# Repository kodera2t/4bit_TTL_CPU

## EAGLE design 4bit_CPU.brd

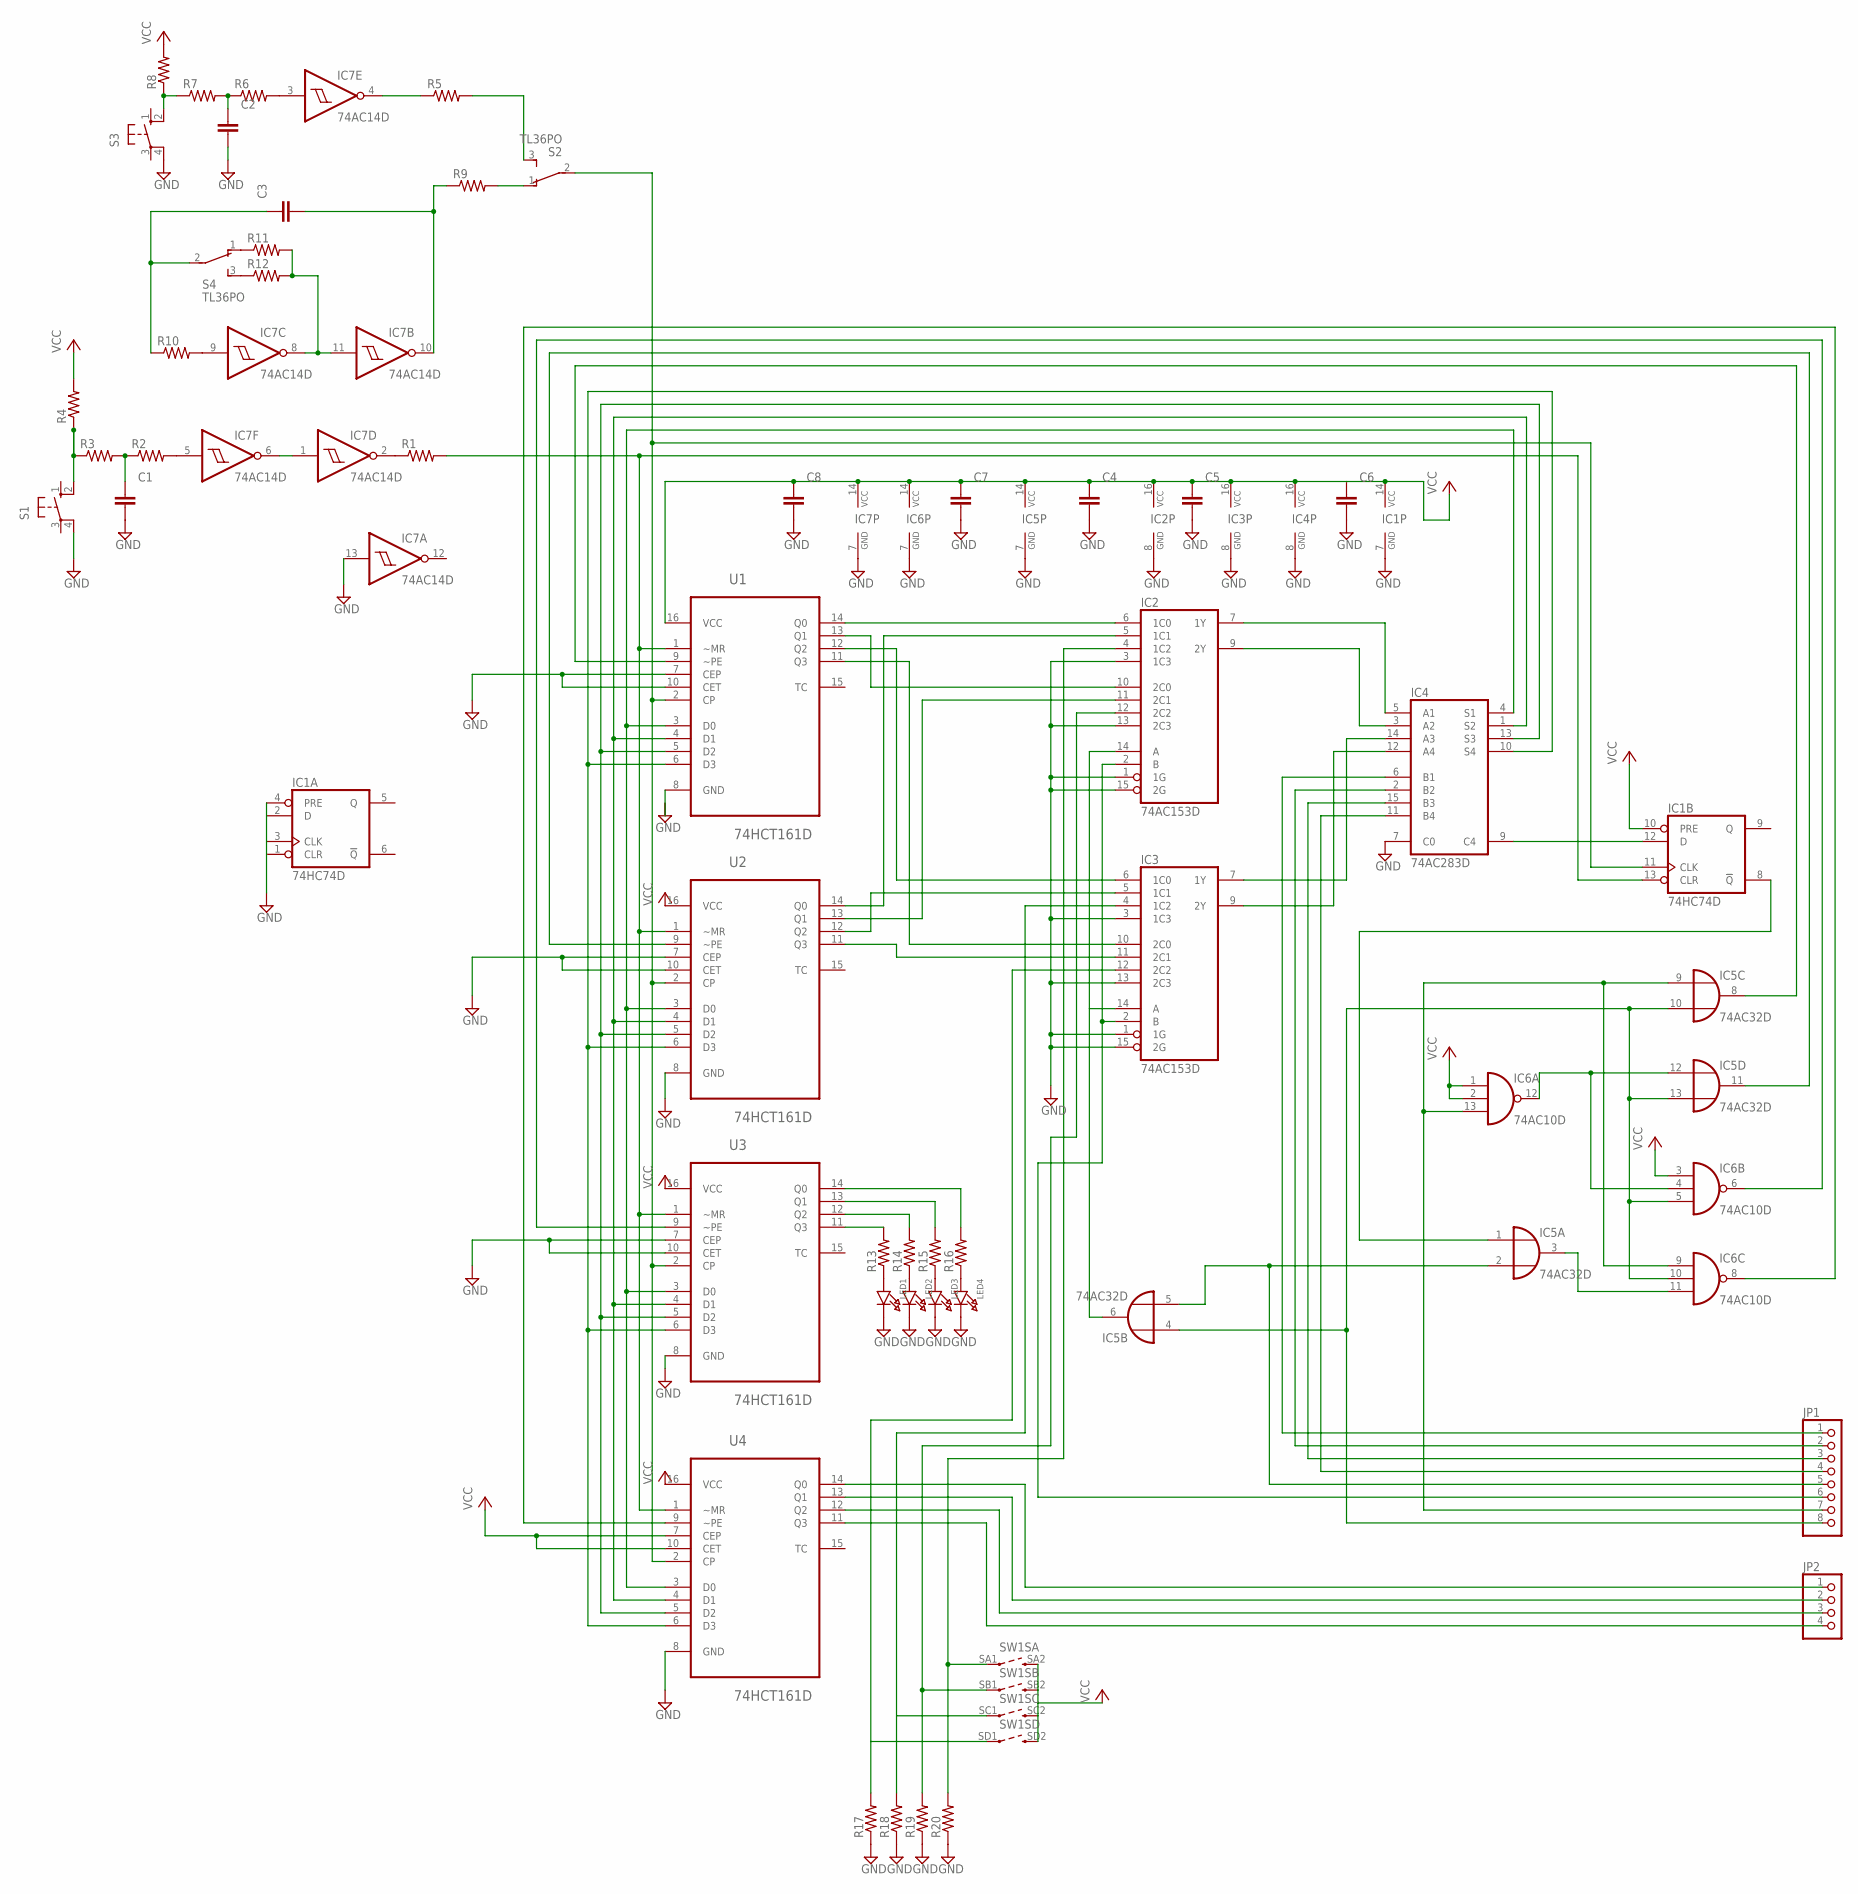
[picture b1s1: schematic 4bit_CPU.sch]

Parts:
C1, C2, C3, C4, C5, C6, C7, C8: CAPACITOR_NPOL-0603; C603
IC1: 74HC74D; SO14
IC2, IC3: 74AC153D; SO16
IC4: 74AC283D; SO16
IC5: 74AC32D; SO14
IC6: 74AC10D; SO14
IC7: 74AC14D; SO14
JP1: HEADER-1X8; 1X08_OVAL
JP2: HEADER-1X4; 1X04_OVAL
LED1, LED2, LED3, LED4: LED0603; CHIPLED_0603
R1, R2, R3, R4, R5, R6, R7, R8, R9, R10, R11, R12, R13, R14, R15, R16, R17, R18, R19, R20: R-US_R0603; R0603
S1, S3: 10-XX; B3F-10XX
S2, S4: TL36PO; TL3XPO
SW1: SW_DIP_4P; SW-SMT-4
U1, U2, U3, U4: 74HCT161D; SOIC127P600X175-16N

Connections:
GND: C1.2, C2.2, C4.2, C5.2, C6.2, C7.2, C8.2, IC1.1 (CLR), IC1.2 (D), IC1.3 (CLK), IC1.4 (PRE), IC1.7 (GND), IC2.1 (1G), IC2.3 (1C3), IC2.8 (GND), IC2.13 (2C3), IC2.15 (2G), IC3.1 (1G), IC3.3 (1C3), IC3.8 (GND), IC3.13 (2C3), IC3.15 (2G), IC4.7 (C0), IC4.8 (GND), IC5.7 (GND), IC6.7 (GND), IC7.7 (GND), IC7.13 (I), LED1.C, LED2.C, LED3.C, LED4.C, R17.1, R18.1, R19.1, R20.1, S1.4 (P1), S3.4 (P1), U1.7 (CEP), U1.10 (CET), U2.7 (CEP), U2.8 (GND), U2.10 (CET), U3.7 (CEP), U3.8 (GND), U3.10 (CET), U4.8 (GND)
unnamed: IC2.14 (A), IC3.14 (A), IC5.6 (O)
unnamed: IC2.2 (B), IC3.2 (B), JP1.6
unnamed: IC2.6 (1C0), U1.14 (Q0)
unnamed: IC2.5 (1C1), U2.14 (Q0)
unnamed: IC2.10 (2C0), U1.13 (Q1)
unnamed: IC3.6 (1C0), U1.12 (Q2)
unnamed: IC3.5 (1C1), U2.12 (Q2)
unnamed: IC3.10 (2C0), U1.11 (Q3)
unnamed: IC3.11 (2C1), U2.11 (Q3)
unnamed: IC2.11 (2C1), U2.13 (Q1)
unnamed: IC2.7 (1Y), IC4.5 (A1)
unnamed: IC2.9 (2Y), IC4.3 (A2)
unnamed: IC3.7 (1Y), IC4.14 (A3)
unnamed: IC3.9 (2Y), IC4.12 (A4)
unnamed: JP2.1, U4.14 (Q0)
unnamed: IC1.11 (CLK), S2.2, U1.2 (CP), U2.2 (CP), U3.2 (CP), U4.2 (CP)
unnamed: IC1.12 (D), IC4.9 (C4)
unnamed: IC1.13 (CLR), R1.2, U1.1 (~MR), U2.1 (~MR), U3.1 (~MR), U4.1 (~MR)
unnamed: IC4.4 (S1), U1.3 (D0), U2.3 (D0), U3.3 (D0), U4.3 (D0)
unnamed: IC4.1 (S2), U1.4 (D1), U2.4 (D1), U3.4 (D1), U4.4 (D1)
unnamed: IC4.13 (S3), U1.5 (D2), U2.5 (D2), U3.5 (D2), U4.5 (D2)
unnamed: IC4.10 (S4), U1.6 (D3), U2.6 (D3), U3.6 (D3), U4.6 (D3)
unnamed: IC5.9 (I0), IC6.9 (I0), IC6.13 (I2), JP1.7
unnamed: IC5.4 (I0), IC5.10 (I1), IC5.13 (I1), IC6.5 (I2), IC6.10 (I1), JP1.8
unnamed: IC5.12 (I0), IC6.4 (I1), IC6.12 (O)
unnamed: IC5.3 (O), IC6.11 (I2)
unnamed: IC1.8 (!Q), IC5.1 (I0)
unnamed: IC5.2 (I1), IC5.5 (I1), JP1.5
unnamed: R5.2, S2.3 (S)
unnamed: IC5.8 (O), U1.9 (~PE)
unnamed: IC5.11 (O), U2.9 (~PE)
unnamed: IC6.6 (O), U3.9 (~PE)
unnamed: IC6.8 (O), U4.9 (~PE)
unnamed: IC7.2 (O), R1.1
unnamed: IC7.1 (I), IC7.6 (O)
unnamed: IC7.5 (I), R2.2
unnamed: C1.1, R2.1, R3.2
unnamed: R3.1, R4.1, S1.2 (S1)
unnamed: IC7.4 (O), R5.1
unnamed: IC7.3 (I), R6.2
unnamed: C2.1, R6.1, R7.2
unnamed: R7.1, R8.1, S3.2 (S1)
unnamed: R9.2, S2.1 (O)
unnamed: IC7.8 (O), IC7.11 (I), R11.2, R12.2
unnamed: C3.2, IC7.10 (O), R9.1
unnamed: IC7.9 (I), R10.2
unnamed: JP2.2, U4.13 (Q1)
unnamed: R11.1, S4.1 (O)
unnamed: R12.1, S4.3 (S)
unnamed: C3.1, R10.1, S4.2
unnamed: IC4.11 (B4), JP1.4
unnamed: IC4.15 (B3), JP1.3
unnamed: IC4.2 (B2), JP1.2
unnamed: IC4.6 (B1), JP1.1
unnamed: JP2.3, U4.12 (Q2)
unnamed: JP2.4, U4.11 (Q3)
unnamed: R13.2, U3.11 (Q3)
unnamed: R14.2, U3.12 (Q2)
unnamed: R15.2, U3.13 (Q1)
unnamed: R16.2, U3.14 (Q0)
unnamed: LED1.A, R13.1
unnamed: LED2.A, R14.1
unnamed: LED3.A, R15.1
unnamed: LED4.A, R16.1
unnamed: IC2.4 (1C2), R20.2, SW1.SA1 (1)
unnamed: IC2.12 (2C2), R19.2, SW1.SB1 (1)
unnamed: IC3.4 (1C2), R18.2, SW1.SC1 (1)
unnamed: IC3.12 (2C2), R17.2, SW1.SD1 (1)
VCC: C4.1, C5.1, C6.1, C7.1, C8.1, IC1.10 (PRE), IC1.14 (VCC), IC2.16 (VCC), IC3.16 (VCC), IC4.16 (VCC), IC5.14 (VCC), IC6.1 (I0), IC6.2 (I1), IC6.3 (I0), IC6.14 (VCC), IC7.14 (VCC), R4.2, R8.2, SW1.SA2 (2), SW1.SB2 (2), SW1.SC2 (2), SW1.SD2 (2), U1.16 (VCC), U2.16 (VCC), U3.16 (VCC), U4.7 (CEP), U4.10 (CET), U4.16 (VCC)

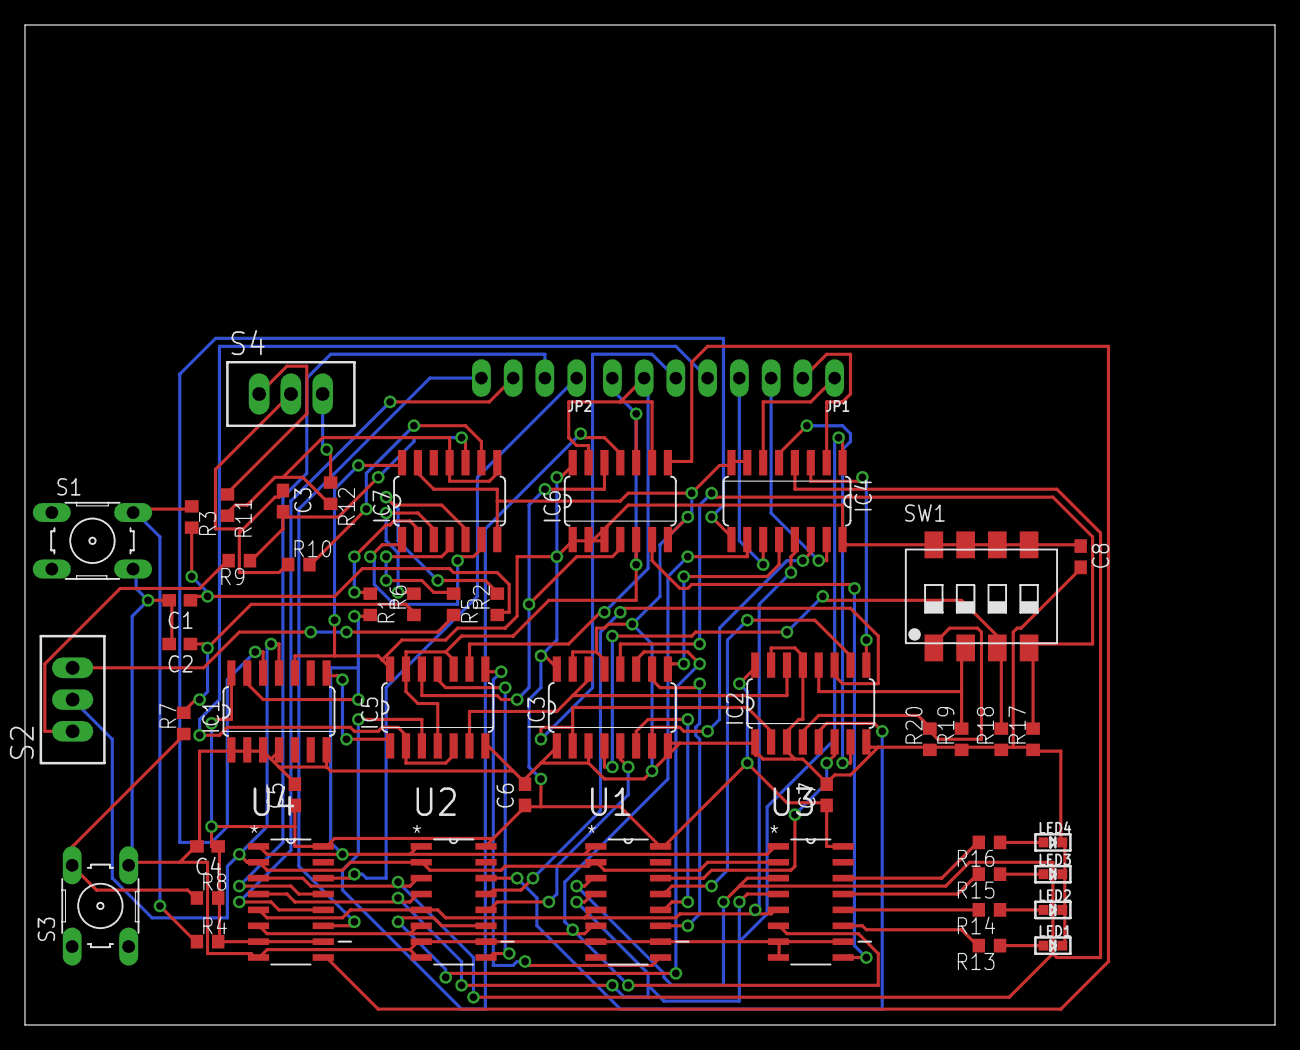
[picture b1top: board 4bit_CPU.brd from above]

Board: 2 copper layers, 100.0 x 80.0 mm, 50 parts (0 on the bottom side), 70 nets.

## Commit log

2015-11-15 initial submission

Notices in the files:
parts and their libraries:
OLED_mod: This work is placed in the public domain, and may be freely used for commercial and non-commercial work with the following conditions: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
